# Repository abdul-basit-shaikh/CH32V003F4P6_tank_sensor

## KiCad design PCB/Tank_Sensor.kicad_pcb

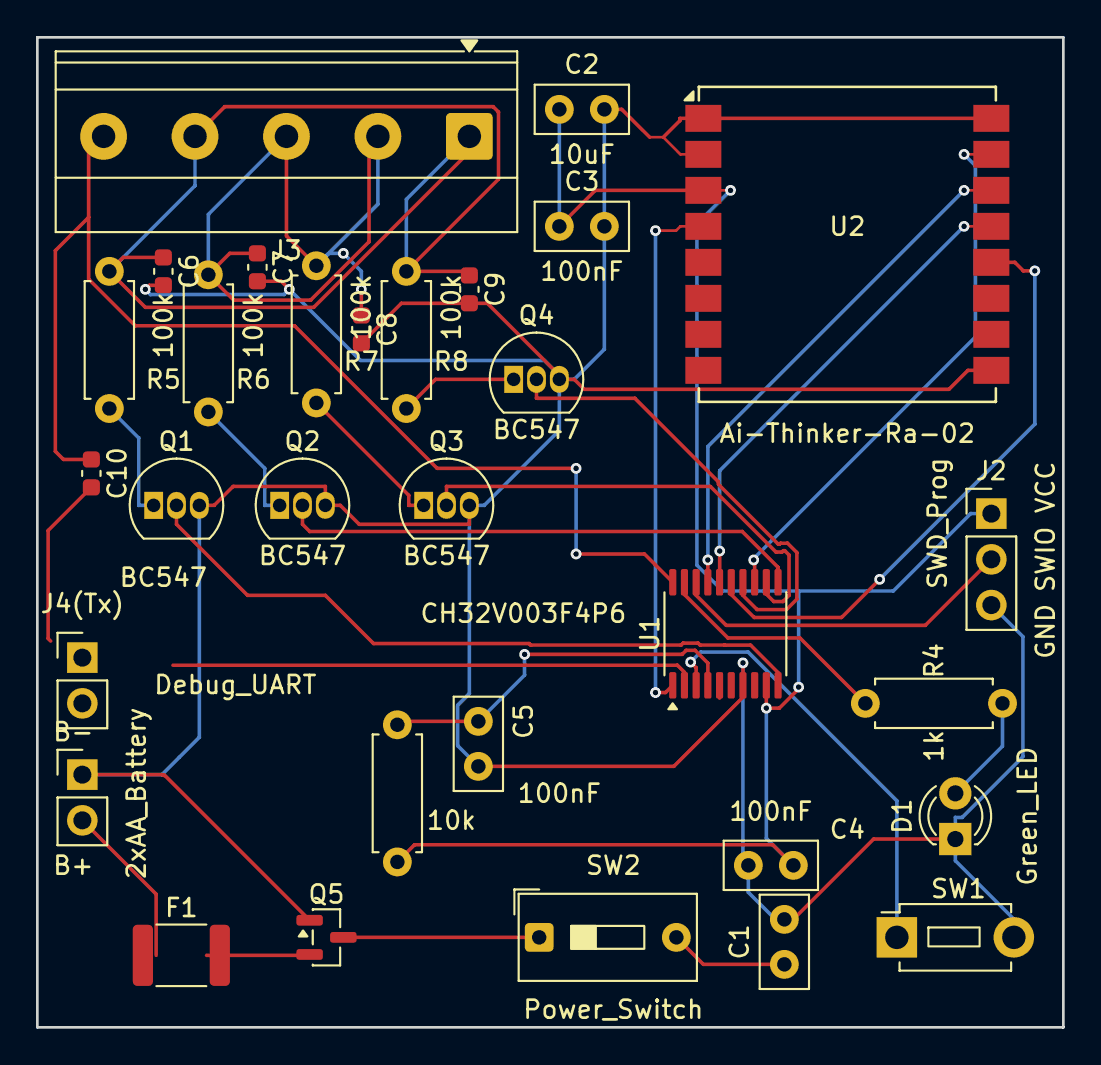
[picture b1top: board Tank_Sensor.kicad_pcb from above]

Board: 2 copper layers, 57.0 x 55.0 mm, 31 parts (0 on the bottom side), 27 nets.

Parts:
B-: 2xAA_Battery; PinHeader_1x02_P2.54mm_Vertical
C1: 100uF; C_Disc_D5.0mm_W2.5mm_P2.50mm
C2: 10uF; C_Disc_D5.0mm_W2.5mm_P2.50mm
C3, C4, C5: 100nF; C_Disc_D5.0mm_W2.5mm_P2.50mm
C6, C7, C8, C9, C10: 100nF; C_0603_1608Metric
D1: Green_LED; LED_D3.0mm
F1: 500mA_PTC; Fuse_1812_4532Metric
J2: SWD_Prog; PinHeader_1x03_P2.54mm_Vertical
J3: Sensor_Conn; TerminalBlock_Phoenix_MKDS-1,5-5-5.08_1x05_P5.08mm_Horizont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
J4(Tx): Debug_UART; PinHeader_1x02_P2.54mm_Vertical
Q1, Q2, Q3, Q4: BC547; TO-92_Inline
Q5: AO3401A; SOT-23
R3: 10k; R_Axial_DIN0207_L6.3mm_D2.5mm_P7.62mm_Horizontal
R4: 1k; R_Axial_DIN0207_L6.3mm_D2.5mm_P7.62mm_Horizontal
R5, R6, R7, R8: 100k; R_Axial_DIN0207_L6.3mm_D2.5mm_P7.62mm_Horizontal
SW1: BTN_6mm; SW_PUSH_1P1T_6x3.5mm_H5.0_APEM_MJTP1250
SW2: Power_Switch; SW_DIP_SPSTx01_Slide_9.78x4.72mm_W7.62mm_P2.54mm
U1: CH32V003F4P6; TSSOP-20_4.4x6.5mm_P0.65mm
U2: Ai-Thinker-Ra-02; Ai-Thinker-Ra-01-LoRa

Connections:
/BTN: SW1.1, U1.3 (PD6)
/LED_A: D1.2 (A), R4.2
/LED_DRIVE: R4.1, U1.19 (PD2)
/LORA_NSS: U1.13 (PC3/NSS), U2.15 (~NSS)
/LORA_RST: U1.1 (PD4), U2.4 (~RESET)
/NRST: C5.1, R3.2, U1.4 (~NRST/PD7)
/PROBE_25: C6.1, J3.1, R5.1
/PROBE_50: C7.1, J3.2, R6.1
/PROBE_75: C8.1, J3.3, R7.1
/PROBE_100: C9.1, J3.4, R8.1
/Q1_B: Q1.1 (B), R5.2
/Q2_B: Q2.1 (B), R6.2
/Q3_B: Q3.1 (B), R7.2
/Q4_B: Q4.1 (B), R8.2
/SENSOR_25: Q1.2 (C), U1.10 (PC0)
/SENSOR_50: Q2.2 (C), U1.11 (PC1)
/SENSOR_75: Q3.2 (C), U1.12 (PC2)
/SENSOR_100: Q4.2 (C), U1.14 (PC4)
/SPI_MISO: U1.17 (PC7/MISO), U2.14 (MOSI)
/SPI_MOSI: U1.16 (PC6/MOSI), U2.13 (MISO)
/SPI_SCK: U1.15 (PC5/SCK), U2.12 (SCK)
/SWIO: J2.2, U1.18 (PD1/SWIO)
/UART_TX: J4(Tx).1, U1.2 (PD5/UTX)
GND: B-.1, C1.2, C2.2, C3.2, C4.2, C5.2, C6.2, C7.2, C8.2, C9.2, C10.2, D1.1 (K), J2.3, J4(Tx).2, Q1.3 (E), Q2.3 (E), Q3.3 (E), Q4.3 (E), Q5.1 (G), SW1.2, U1.7 (VSS), U2.1 (GND), U2.2 (GND), U2.9 (GND), U2.16 (GND)
unnamed: Q5.3 (D), SW2.1
unnamed: F1.2, Q5.2 (S)
VCC: C1.1, C2.1, C3.1, C4.1, J2.1, R3.1, SW2.2, U1.9 (VDD), U1.20 (PD3), U2.3 (VDD)

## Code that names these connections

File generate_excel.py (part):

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    [3, "Q6", "P-Channel MOSFET", "AO3401A / SI2301 (30V, 4.2A, Low Rds(on))", "SOT-23", 1, 
     "Anti-Corrosion High-Side Switch. Paani ke common wire me 24/7 current nahi bhejta. Jab MCU reading leta hai sirf 10ms ke liye VCC pulse deta hai, baki waqt paani me 0V rehta hai taaki probes rust/electrolysis se kharab na hon.", 
     "https://robu.in/?s=AO3401A+MOSFET&post_type=product", 
     "Gate connected to PD3 via 100k pull-up."],
     
    [4, "Q1", "NPN Transistor (25% Probe)", "BC547 / 2N3904 / MMBT3904", "TO-92 / SOT-23", 1, 
     "25% Water Level Buffer. Paani 25% probe ko touch karta hai toh base trigger hokar Collector (PC0) ko LOW (0V) pull karta hai.", 
     "https://robu.in/?s=BC547+Transistor&post_type=product", 
     "Emitter to GND, Base via 100k resistor."],
     
    [5, "Q2", "NPN Transistor (50% Probe)", "BC547 / 2N3904 / MMBT3904", "TO-92 / SOT-23", 1, 
     "50% Water Level Buffer. 50% level touch hone par Collector (PC1) ko LOW pull karta hai.", 
     "https://robu.in/?s=BC547+Transistor&post_type=product", 
     "Emitter to GND, Base via 100k resistor."],
     
    [6, "Q3", "NPN Transistor (75% Probe)", "BC547 / 2N3904 / MMBT3904", "TO-92 / SOT-23", 1, 
     "75% Water Level Buffer. 75% level touch hone par Collector (PC2) ko LOW pull karta hai.", 
     "https://robu.in/?s=BC547+Transistor&post_type=product", 
     "Emitter to GND, Base via 100k resistor."],
     
    [7, "Q4", "NPN Transistor (100% Probe)", "BC547 / 2N3904 / MMBT3904", "TO-92 / SOT-23", 1, 
     "100% Water Level Buffer. 100% level touch hone par Collector (PC4) ko LOW pull karta hai.", 
     "https://robu.in/?s=BC547+Transistor&post_type=product", 
     "Emitter to GND, Base via 100k resistor."],
     
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     "NRST to VDD."],
     
    [20, "R4", "LED Resistor", "1kΩ 5% (0.125W)", "0603 / 0805 SMD", 1, 
     "LED Current Limiter. Status LED (PD2) ko safe 1-2mA current deta hai taaki battery waste na ho.", 
     "https://robu.in/?s=1k+0805+SMD+Resistor&post_type=product", 
     "PD2 to LED Anode."],
     
    [21, "R5-R8", "Probe Base Resistors", "4x 100kΩ 5% (0.125W)", "0603 / 0805 SMD", 4, 
     "Transistor Base Current Limiter. Q1-Q4 BC547 ke base me safe micro-ampere current allow karte hain jab paani touch hota hai.", 
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     "Probe lines to Base pins."],
     
    [22, "R9", "MOSFET Gate Pull-up Resistor", "100kΩ 5% (0.125W)", "0603 / 0805 SMD", 1, 
     "Q6 Gate Lock. PD3 floating hone par ya deep sleep ke waqt Q6 Gate ko VCC se pull karke MOSFET ko 100% OFF rakhta hai.", 
     "https://robu.in/?s=100k+0805+SMD+Resistor&post_type=product", 
     "Q6 Gate to VCC."],
     
    [23, "D1", "Status Indicator LED", "3mm Green LED / 0805 SMD", "SMD / TH", 1, 
     "User Feedback. Pairing mode, reset indication, aur data transmission confirmation blink karne ke liye.", 
     "https://robu.in/?s=Green+LED+0805&post_type=product", 
     "Active HIGH from PD2."],
     
    [24, "SW1", "User Push Button", "6x6mm Tactile Switch", "SMD / TH", 1, 
     "Pairing & Reset. 3s hold = Reboot, 5s hold = Controller ke saath Pairing Mode.", 
     "https://robu.in/?s=Tactile+Push+Button+6x6&post_type=product", 
     "Active LOW connected to PD6."],
     
    [25, "SW2", "Power Slide Switch", "SPST Slide Switch 3-Pin", "Through-Hole", 1, 
     "Battery ON/OFF Switch. Board ko storage ya maintenance ke waqt physically switch off karne ke liye.", 
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     "Polarized connector recommended."],
     
    [27, "J2", "SWD Programming Header", "1x3 Male Header (2.54mm)", "Through-Hole", 1, 
     "Firmware Flashing. WCH-LinkE programmer se code upload karne ke liye (VCC, SWIO/PD1, GND).", 
     "https://robu.in/?s=2.54mm+Male+Berg+Strip&post_type=product", 
     "Single-wire debug header."],
     
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     "Heavy duty screw terminal."],
     
    [29, "J4", "Debug UART Header", "1x2 Male Header (2.54mm)", "Through-Hole", 1, 
     "Serial monitor debugging ke liye (PD5 TX + GND).", 
     "https://robu.in/?s=2.54mm+Male+Berg+Strip&post_type=product", 
     "Optional for debugging."],
     
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ws_pins = wb_tank.create_sheet(title="MCU_Pin_Mapping")
pin_headers = ["TSSOP-20 Pin", "Pin Name", "Connected Component / Signal", "Direction / Mode", "Description & Circuit Function"]
pin_data = [
    ["Pin 1", "PD4", "SX1278 LoRa RST", "Output", "LoRa Module Hardware Reset Line"],
    ["Pin 2", "PD5", "J4 Debug UART TX", "Output", "115200 Baud Serial Debug Print (Optional)"],
    ["Pin 3", "PD6", "SW1 Push Button", "Input (Pull-Up)", "Pairing / Reset / Reboot Button (Active LOW, EXTI Wakeup)"],
    ["Pin 4", "PD7", "NRST (R3 10k + C5 104)", "Input / Reset", "MCU Hardware Reset with RC Noise Filter"],
    ["Pin 5", "PA1", "NC (Internal Vref used)", "Analog Input", "Battery monitored via 1.20V Internal Bandgap (0µA drain)"],
    ["Pin 6", "PA2", "NC", "Spare GPIO", "Unconnected / Spare Test Pad"],
    ["Pin 7", "VSS", "Ground Plane (GND)", "Power", "Main System Ground"],
    ["Pin 8", "PD0", "NC", "Spare GPIO", "Unconnected / Spare Test Pad"],
    ["Pin 9", "VDD", "VCC Rail (3.0V - 3.3V) + C4 (104)", "Power", "Main MCU Power Input (with 100nF Decoupling Cap)"],
    ["Pin 10", "PC0", "Q1 Collector (25% Probe)", "Input (Pull-Up)", "25% Water Level Detector (Reads LOW when water reaches 25%)"],
    ["Pin 11", "PC1", "Q2 Collector (50% Probe)", "Input (Pull-Up)", "50% Water Level Detector (Reads LOW when water reaches 50%)"],
    ["Pin 12", "PC2", "Q3 Collector (75% Probe)", "Input (Pull-Up)", "75% Water Level Detector (Reads LOW when water reaches 75%)"],
    ["Pin 13", "PC3", "SX1278 LoRa NSS (CS)", "Output", "SPI Chip Select for SX1278 LoRa Module"],
    ["Pin 14", "PC4", "Q4 Collector (100% Probe)", "Input (Pull-Up)", "100% Water Level Detector (Reads LOW when water reaches 100%)"],
    ["Pin 15", "PC5", "SX1278 LoRa SCK", "AF Output", "SPI1 Clock Line for LoRa Communication"],
    ["Pin 16", "PC6", "SX1278 LoRa MOSI", "AF Output", "SPI1 Master-Out-Slave-In Data Line"],
    ["Pin 17", "PC7", "SX1278 LoRa MISO", "Input (Pull-Up)", "SPI1 Master-In-Slave-Out Data Line"],
    ["Pin 18", "PD1", "J2 SWIO Header", "Bidirectional", "Single-Wire Debug / Flash Programming Interface"],
    ["Pin 19", "PD2", "D1 Status LED (via R4 1k)", "Output", "Status Indicator LED (Active HIGH: Blinks for TX, Pairing)"],
    ["Pin 20", "PD3", "Q6 P-MOSFET Gate (via R9 100k)", "Output", "Common Probe Driver (Active LOW: Pulsed 3V for 10ms)"]
]
ws_pins.cell(row=1, column=1, value="CH32V003F4P6 TSSOP-20 COMPLETE PIN MAPPING")
ws_pins.append(pin_headers)
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     "Connected between GPIO 5 and Base."],
     
    [11, "SW1-4", "User Input Buttons (4x)", "TTP223 Touch Modules / 6x6mm Tactile Buttons", "Module / SMD / TH", 4, 
     "User Controls: Btn 1: Menu/Select (GPIO 3), Btn 2: Pump 1 (GPIO 0), Btn 3: Pump 2 (GPIO 1), Btn 4: Pump 3 (GPIO 2).", 
     "https://robu.in/?s=TTP223+Touch+Sensor&post_type=product", 
     "Active HIGH signals. TTP223 capacitive touch recommended for modern look."],
     
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    ["GPIO 18", "LORA_SCK_PIN", "SX1278 LoRa SCK", "SPI Clock Output", "SPI Clock for LoRa Communication"],
    ["GPIO 19", "LORA_MOSI_PIN", "SX1278 LoRa MOSI", "SPI Master Out", "SPI Master Out to LoRa Module"],
    ["GPIO 4", "LORA_MISO_PIN", "SX1278 LoRa MISO", "SPI Master In", "SPI Master In from LoRa Module"],
    ["GPIO 23", "LORA_NSS_PIN", "SX1278 LoRa NSS (CS)", "SPI Chip Select (Output)", "Active LOW Chip Select for LoRa"],
    ["GPIO 22", "LORA_RST_PIN", "SX1278 LoRa RST", "Output", "Hardware Reset Pin for LoRa Module"],
    ["GPIO 21", "LORA_DIO0_PIN", "SX1278 LoRa DIO0", "Input (Interrupt)", "Packet Received / Transmit Done Interrupt"],
    ["GPIO 7", "I2C_MASTER_SCL_IO", "OLED Display & DS3231 RTC SCL", "I2C Clock Output", "Shared I2C Clock Line (400kHz Fast Mode)"],
    ["GPIO 6", "I2C_MASTER_SDA_IO", "OLED Display & DS3231 RTC SDA", "I2C Data (Bidirectional)", "Shared I2C Data Line"],
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
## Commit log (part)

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2026-01-26 acches connection ban raha hai
2026-01-26 perfect chal raha hai
2026-01-26 tank level ky liye pin or button or led ky pin set kr diya hai or data abhi ja raha hai or recveed bhi ho raha hai water level controller pr sahi se
2026-02-07 jab reset button pressed kary gy to tank id change hogi
2026-02-21 sanser first time add ho raha tha sirf os ko fixed kiya hai abhi kitne bar bhi add karo to jo ta hai
2026-02-21 Add CRC check
2026-02-21 added micro for pairig time ad add blik pattern
2026-02-21 add battery pin ad feature and flash memory(save tak id ,other)
2026-02-21 factory reset
2026-02-24 remove security code concept
2026-02-24 jab water level chagne hoti hai or har 4hr mai device details send kary ga is se battery consumtion kam ho ga
2026-02-24 power down or deep sleep feature added but need to more improvement on it
2026-02-28 Enable Hardware CRC, optimize RF power, and improve sensor stability logic
2026-02-28 singal click pr restart longpressed pr factory reset
2026-03-01 Probe Fault Detected!
2026-03-01 DEBUG_PRINT micro added
2026-03-01 BOOT_SAFETY_DELAY_MS 5000(5s)
2026-03-01 normal error solved
2026-03-07 Jo probe dtect nahi ho gi os ki information send ho gi
2026-04-04 level reading pattern change
2026-04-19 ack update
2026-04-19 jab ek sath water level dectect hota hai s time sahi kam kr ta hai
2026-04-19 battery ki range 2.7 to 3.3v kiya hai
2026-04-19 memory optiimized kary hai is mai or FLOATING to IPU (pin MISO PC7)
2026-04-19 pairing time ko sahi kiya hai is mai
